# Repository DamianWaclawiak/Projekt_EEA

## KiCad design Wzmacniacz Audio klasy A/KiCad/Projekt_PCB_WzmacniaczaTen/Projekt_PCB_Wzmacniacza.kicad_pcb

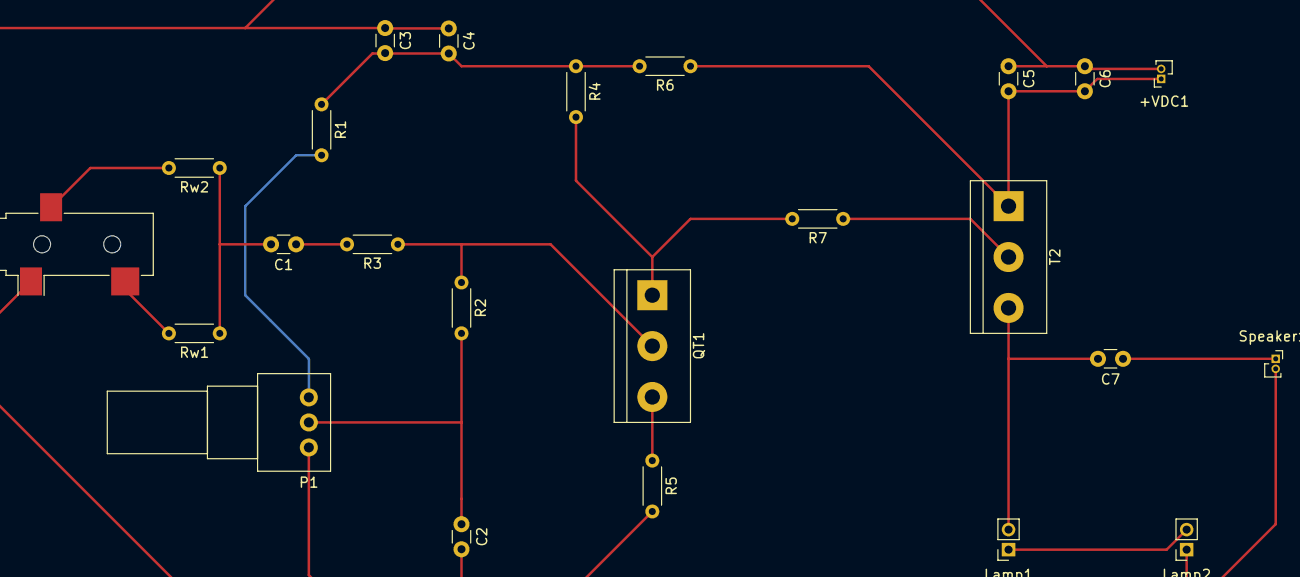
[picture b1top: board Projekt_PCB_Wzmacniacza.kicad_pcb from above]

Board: 2 copper layers, 24 parts (0 on the bottom side), 16 nets.

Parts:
+VDC1: Conn_01x02_Female; PinSocket_1x02_P1.00mm_Vertical
C1: 2.2u; C_Disc_D3.0mm_W1.6mm_P2.50mm
C2: 100u; C_Disc_D3.0mm_W1.6mm_P2.50mm
C3: 220u; C_Disc_D3.0mm_W1.6mm_P2.50mm
C4, C6: 100n; C_Disc_D3.0mm_W1.6mm_P2.50mm
C5, C7: 4700u; C_Disc_D3.0mm_W1.6mm_P2.50mm
JackWejście1: AudioJack3; Jack_3.5mm_CUI_SJ-3523-SMT_Horizontal
Lamp1, Lamp2: 12V 21W; PinSocket_1x02_P2.00mm_Vertical
P1: 1K; Potentiometer_Alps_RK097_Single_Horizontal
QT1: BC550C; TerminalBlock_bornier-3_P5.08mm
R1, R4: 2.2K; R_Axial_DIN0204_L3.6mm_D1.6mm_P5.08mm_Horizontal
R2: 22K; R_Axial_DIN0204_L3.6mm_D1.6mm_P5.08mm_Horizontal
R3, R5: 330; R_Axial_DIN0204_L3.6mm_D1.6mm_P5.08mm_Horizontal
R6, R7: 100; R_Axial_DIN0204_L3.6mm_D1.6mm_P5.08mm_Horizontal
Rw1, Rw2: 1.5K; R_Axial_DIN0204_L3.6mm_D1.6mm_P5.08mm_Horizontal
Speaker1: Conn_01x02_Female; PinSocket_1x02_P1.00mm_Vertical
T2: IRFZ44; TerminalBlock_bornier-3_P5.08mm

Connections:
GND: +VDC1.2, C2.2, C3.1, C4.1, C5.1, C6.1, JackWejście1.S, Lamp2.1, P1.3, R5.2, Speaker1.2
unnamed: +VDC1.1, C5.2, C6.2, R6.1, T2.1
unnamed: C1.1, R3.2
unnamed: C1.2, Rw1.1, Rw2.1
unnamed: C2.1, P1.2, R2.2
unnamed: C3.2, C4.2, R1.1, R4.1, R6.2
unnamed: C7.1, Speaker1.1
unnamed: C7.2, Lamp1.2, T2.3
unnamed: JackWejście1.R, Rw2.2
unnamed: JackWejście1.T, Rw1.2
unnamed: Lamp1.1, Lamp2.2
unnamed: P1.1, R1.2
unnamed: QT1.1, R4.2, R7.2
unnamed: QT1.2, R2.1, R3.1
unnamed: QT1.3, R5.1
unnamed: R7.1, T2.2
